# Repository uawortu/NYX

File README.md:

# NYX
A compact ESP32-S3-based multifunctional keychain device featuring audio playback, voice recording, motion-triggered actions, customizable reminders, and seamless internet connectivity with integrated SD card storage and battery management

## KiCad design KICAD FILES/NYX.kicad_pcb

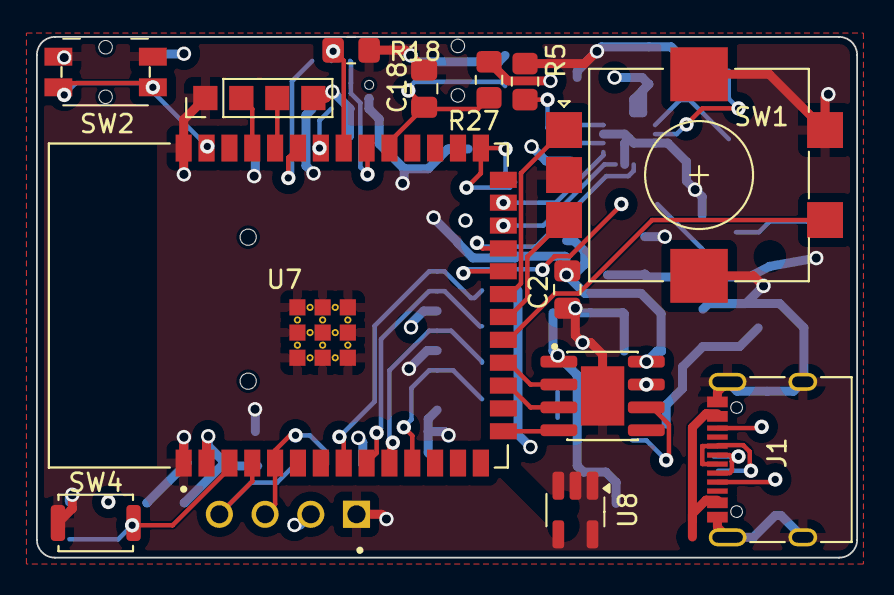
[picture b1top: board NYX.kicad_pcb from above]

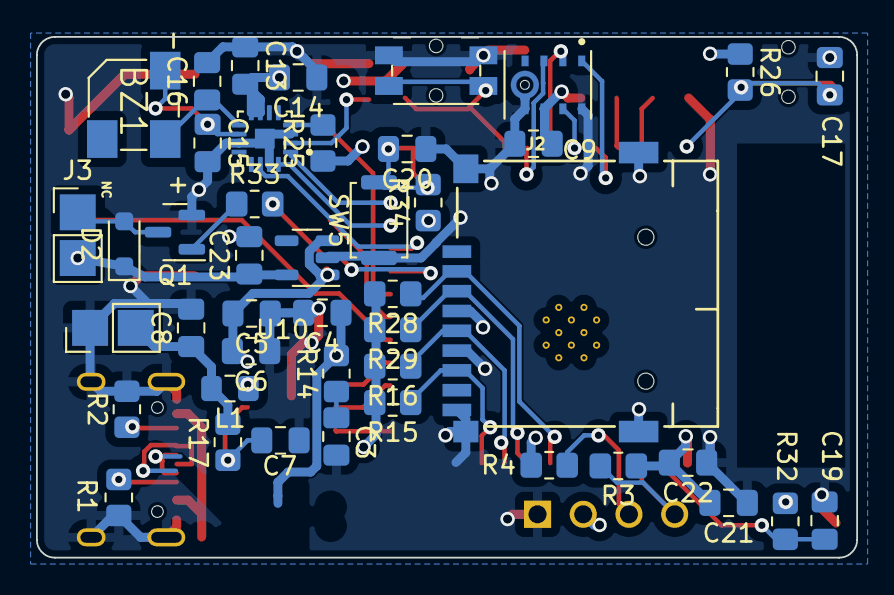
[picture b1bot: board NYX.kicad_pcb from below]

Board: 4 copper layers, 45.6 x 28.9 mm, 58 parts (44 on the bottom side), 46 nets.

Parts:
BZ1: Buzzer; CUI_CSS-0575A-SMT
C2, C13, C22, C23: 10uF; C_0805_2012Metric_Pad1.18x1.45mm_HandSolder
C3, C4, C5, C6, C7, C8, C9, C15, C16, C17, C18, C19, C20: C; C_0805_2012Metric_Pad1.18x1.45mm_HandSolder
C14, C21: 0.1uF; C_0805_2012Metric_Pad1.18x1.45mm_HandSolder
D2: 1N4148WT; D_SOD-323_HandSoldering
J1: USB_C_Receptacle_USB2.0; USB_C_Receptacle_XKB_U262-16XN-4BVC11
J2: Micro_SD_Card; J_SD_Card-micro_socket_A
J3, J5: Conn_01x02_Pin; PinHeader_1x02_P2.54mm_Vertical
J4: Conn_01x04; PinHeader_1x04_P2.00mm_Vertical
L1: 1uH; L_0805_2012Metric_Pad1.15x1.40mm_HandSolder
MK1: INMP441; MIC_INMP441
Q1: MMBT3904; SOT-23
R1, R2: 5.1k; R_0805_2012Metric_Pad1.20x1.40mm_HandSolder
R3, R4: 4.7K; R_0805_2012Metric_Pad1.20x1.40mm_HandSolder
R5, R18, R25: 100K; R_0805_2012Metric_Pad1.20x1.40mm_HandSolder
R14, R17, R26, R27: R; R_0805_2012Metric_Pad1.20x1.40mm_HandSolder
R15, R16, R28, R29, R32, R33, R34: 10K; R_0805_2012Metric_Pad1.20x1.40mm_HandSolder
SW1: RotaryEncoder_Switch; RotaryEncoder_Alps_EC11E-Switch_Vertical_H20mm_SMD
SW2, SW3: SW_Push_Dual; Panasonic_EVQPUL_EVQPUC
SW4, SW5: SW_Push; SW_Push_SPST_NO_Alps_SKRK
U3: ESP32-S3-WROOM-1-N16R2; XCVR_ESP32-S3-WROOM-1-N16R2
U4: IP5306; SOIC9P127_490X600X170L84X42T330X241N
U6: MAX98357AETE_T; QFN50P300X300X80-17N
U7: DM-OLED096-636; MODULE_DM-OLED096-636
U8: USBLC6-2SC6; SOT-23-5_HandSoldering
U10: XC6220B331MR; SOT-23-5

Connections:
+3.3V: C9.1, C13.2, C14.2, C21.2, C22.2, C23.1, D2.1 (K), J2.4 (VDD), J3.2, J4.4, MK1.7 (VDD), R3.1, R4.1, R15.2, R16.2, R25.1, R26.1, R27.1, R28.2, R29.2, R32.1, R34.1, U3.2 (3V3), U6.7 (VDD), U6.8 (VDD), U7.2 (VCC_IN), U10.5 (VOUT)
+5V: C2.1, C5.2, C6.2, U4.8 (VOUT), U10.1 (VIN), U10.3 (CE)
+5VP: C4.1, J1.A4 (VBUS), J1.A9 (VBUS), J1.B4 (VBUS), J1.B9 (VBUS), R14.2, U4.1 (VCC), U8.5 (VBUS)
+BATT: C8.1, J5.2, L1.2, R17.2
/BCLK: U3.24 (IO47), U6.16 (BCLK)
/BUTTON 1: C17.2, R26.2, SW2.2, U3.39 (IO1)
/BUTTON 2: C18.2, R27.2, SW3.2, U3.31 (IO38)
/CS: J2.2 (DAT3/CD), R28.1, U3.8 (IO15)
/DATA+: U3.14 (IO20), U8.3 (I/O2)
/DATA-: U3.13 (IO19), U8.4 (I/O2)
/DIN: U3.25 (IO48), U6.1 (DIN)
/EN PIN: C19.2, R32.2, SW4.2, U3.3 (EN)
/ENCODER SWITCH: SW1.S1, U3.19 (IO11)
/ENCODER CLK: SW1.A, U3.21 (IO13)
/ENCODER DATA: SW1.B, U3.20 (IO12)
/ESP32 SCK: R4.2, U3.5 (IO5), U7.3 (SCL)
/ESP32 SDA: R3.2, U3.4 (IO4), U7.4 (SDA)
/I2S BIT CLK: MK1.1 (SCK), U3.35 (IO42)
/I2S DATA OUTPUT: MK1.2 (SD), R18.2, U3.33 (IO40)
/I2S WORD SELECT: MK1.3 (WS), U3.32 (IO39)
/IO0: C20.2, R34.2, SW5.2, U3.27 (IO0)
/LED1: U3.18 (IO10), U4.2 (LED1)
/LED2: U3.17 (IO9), U4.3 (LED2)
/LED3: U3.15 (IO3), U4.4 (LED3)
/LRCLK: U3.23 (IO21), U6.14 (LRCLK)
/MIC ON/OFF: MK1.8 (CHIPEN), U3.34 (IO41)
/MISO: J2.7 (DAT0), R15.1, U3.11 (IO18)
/MOSI: J2.3 (CMD), R29.1, U3.9 (IO16)
/SCK: J2.5 (CLK), R16.1, U3.10 (IO17)
/Vibration motor PIN: R33.2, U3.22 (IO14)
GND: C2.2, C3.2, C4.2, C5.1, C6.1, C7.2, C8.2, C9.2, C13.1, C14.1, C15.2, C16.2, C17.1, C18.1, C19.1, C20.1, C21.1, C22.1, C23.2, J1.A1 (GND), J1.A12 (GND), J1.B1 (GND), J1.B12 (GND), J1.S1 (SHIELD), J2.6 (VSS), J2.9 (SHIELD), J4.1, J5.1, MK1.5_1 (GND), MK1.5_2 (GND), MK1.6 (GND), MK1.9 (GND), Q1.2 (E), R1.2, R2.2, R5.2, R18.1, SW1.C, SW1.S2, SW2.1, SW3.1, SW4.1, SW5.1, U3.1 (GND), U3.40 (GND), U3.41_1 (GND), U3.41_2 (GND), U3.41_3 (GND), U3.41_4 (GND), U3.41_5 (GND), U3.41_6 (GND), U3.41_7 (GND), U3.41_8 (GND), U3.41_9 (GND), U4.9 (GND), U6.3 (GND), U6.11 (GND), U6.15 (GND), U6.17 (EP), U7.1 (GND), U8.2 (GND), U10.2 (GND)
unnamed: BZ1.2 (+), C15.1, U6.10 (OUTN)
unnamed: BZ1.1 (-), C16.1, U6.9 (OUTP)
unnamed: C3.1, R14.1
unnamed: D2.2 (A), J3.1, Q1.3 (C)
unnamed: J1.A5 (CC1), R1.1
unnamed: J1.B5 (CC2), R2.1
unnamed: J1.A6 (D+), J1.B6 (D+), U8.1 (I/O1)
unnamed: J1.A7 (D-), J1.B7 (D-)
unnamed: J4.2, U3.37 (TXD0)
unnamed: J4.3, U3.36 (RXD0)
unnamed: Q1.1 (B), R33.1
unnamed: C7.1, R17.1, U4.6 (BAT)
unnamed: L1.1, U4.7 (SW)
unnamed: R5.1, U6.2 (GAIN_SLOT)
unnamed: R25.2, U6.4 (SD_MODE)

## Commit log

2025-03-07 Track the entire NYX folder and its contents
